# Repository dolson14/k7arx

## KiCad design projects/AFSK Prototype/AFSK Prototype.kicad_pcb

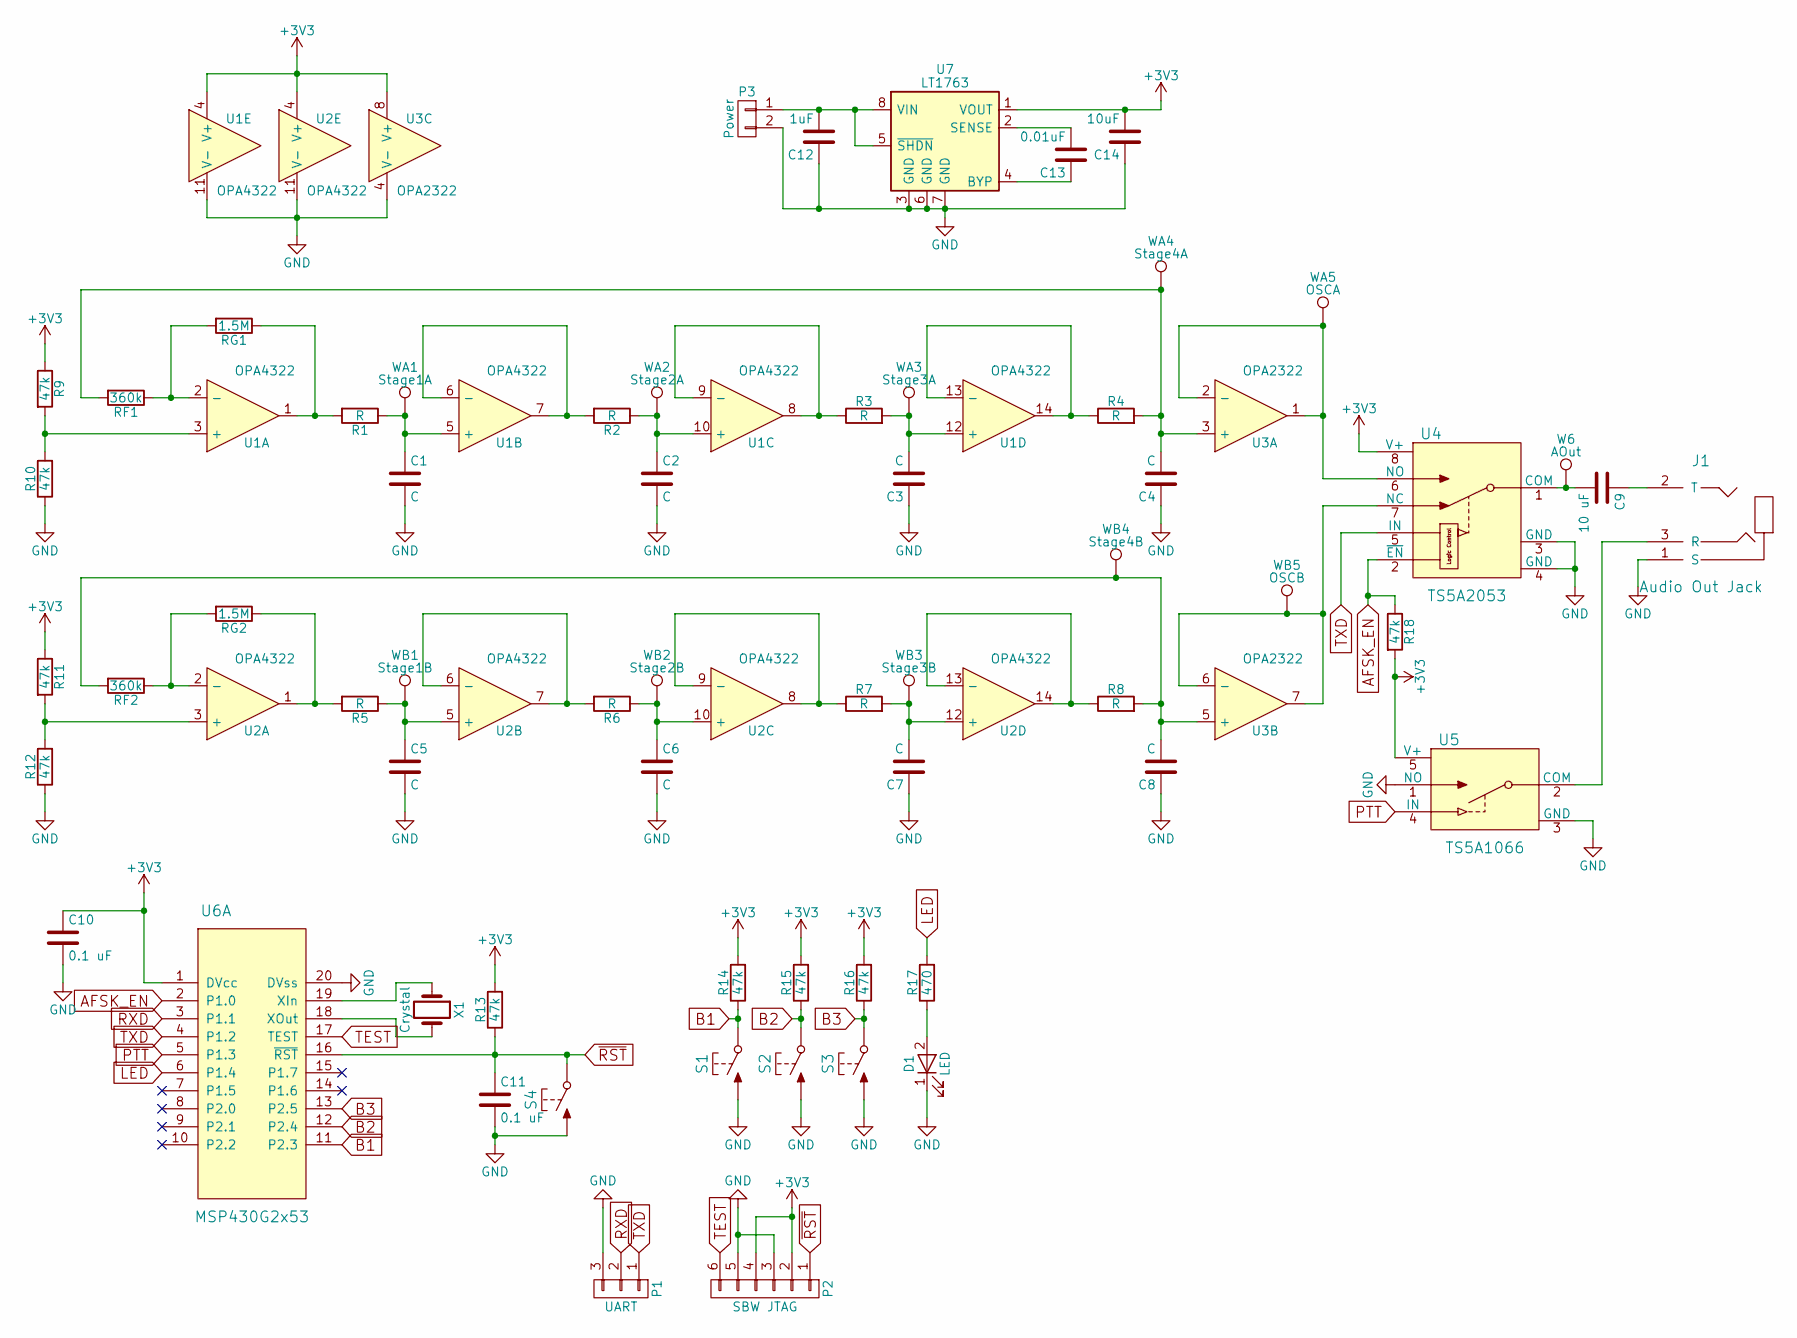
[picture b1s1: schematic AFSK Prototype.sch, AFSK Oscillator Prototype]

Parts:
C1, C2, C3, C4, C5, C6, C7, C8: C; C_0805_HandSoldering
C9: 10 uF; C_0805_HandSoldering
C10, C11: 0.1 uF; C_0805_HandSoldering
C12: 1uF; C_0805_HandSoldering
C13: 0.01uF; C_0805_HandSoldering
C14: 10uF; C_0805_HandSoldering
D1: LED; LED-0805
J1: Audio Out Jack; Jack-TRS-SJ1-3523N
P1: UART; Pin_Header_Straight_1x03
P2: SBW JTAG; Tag-Connect_TC2030-NL
P3: Power; Pin_Header_Straight_1x02
R1, R2, R3, R4, R5, R6, R7, R8: R; R_0805_HandSoldering
R9, R10, R11, R12, R13, R14, R15, R16, R18: 47k; R_0805_HandSoldering
R17: 470; R_0805_HandSoldering
RF1, RF2: 360k; R_0805_HandSoldering
RG1, RG2: 1.5M; R_0805_HandSoldering
S1, S2, S3, S4: TactileSwitch_NO; SPST-EVQ2
U1, U2: OPA4322; PW-14
U3: OPA2322; D
U4: TS5A2053; DCT
U5: TS5A1066; DBV
U6: MSP430G2x53; PW-20
U7: LT1763; SOIC-8-N
W6: AOut; Test_Point
WA1: Stage1A; Test_Point
WA2: Stage2A; Test_Point
WA3: Stage3A; Test_Point
WA4: Stage4A; Test_Point
WA5: OSCA; Test_Point
WB1: Stage1B; Test_Point
WB2: Stage2B; Test_Point
WB3: Stage3B; Test_Point
WB4: Stage4B; Test_Point
WB5: OSCB; Test_Point
X1: Crystal; XTAL-CMR200T

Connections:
+3V3: C10.1, C14.2, P2.2, P2.4, R9.1, R11.1, R13.2, R14.2, R15.2, R16.2, R18.2, U1.4 (V+), U2.4 (V+), U3.8 (V+), U4.8 (V+), U5.5 (V+), U6.1 (DVcc), U7.1 (VOUT)
AFSK_EN: R18.1, U4.2 (~EN), U6.2 (P1.0)
B1: R14.1, S1.2 (COM), U6.11 (P2.3)
B2: R15.1, S2.2 (COM), U6.12 (P2.4)
B3: R16.1, S3.2 (COM), U6.13 (P2.5)
GND: C1.2, C2.2, C3.1, C4.1, C5.2, C6.2, C7.1, C8.1, C10.2, C11.2, C12.1, C14.1, D1.1 (K), J1.1 (S), P1.3, P2.3, P2.5, P3.2, R10.1, R12.1, S1.1 (NO), S2.1 (NO), S3.1 (NO), S4.1 (NO), U1.11 (V-), U2.11 (V-), U3.4 (V-), U4.3 (GND), U4.4 (GND), U5.1 (NO), U5.3 (GND), U6.20 (DVss), U7.3 (GND), U7.6 (GND), U7.7 (GND)
LED: R17.2, U6.6 (P1.4)
unnamed: C1.1, R1.1, U1.5 (+), WA1.1
unnamed: C2.1, R2.1, U1.10 (+), WA2.1
unnamed: C3.2, R3.2, U1.12 (+), WA3.1
unnamed: C4.2, R4.2, RF1.2, U3.3 (+), WA4.1
unnamed: C5.1, R5.1, U2.5 (+), WB1.1
unnamed: C6.1, R6.1, U2.10 (+), WB2.1
unnamed: C7.2, R7.2, U2.12 (+), WB3.1
unnamed: C8.2, R8.2, RF2.2, U3.5 (+), WB4.1
unnamed: C9.1, J1.2 (T)
unnamed: C9.2, U4.1 (COM), W6.1
unnamed: C12.2, P3.1, U7.5 (~SHDN), U7.8 (VIN)
unnamed: C13.1, U7.4 (BYP)
unnamed: C13.2, U7.2 (SENSE)
unnamed: D1.2 (A), R17.1
unnamed: J1.3 (R), U5.2 (COM)
unnamed: R1.2, RG1.1, U1.1
unnamed: R2.2, U1.6 (-), U1.7
unnamed: R3.1, U1.8, U1.9 (-)
unnamed: R4.1, U1.13 (-), U1.14
unnamed: R5.2, RG2.1, U2.1
unnamed: R6.2, U2.6 (-), U2.7
unnamed: R7.1, U2.8, U2.9 (-)
unnamed: R8.1, U2.13 (-), U2.14
unnamed: R9.2, R10.2, U1.3 (+)
unnamed: R11.2, R12.2, U2.3 (+)
unnamed: RF1.1, RG1.2, U1.2 (-)
unnamed: RF2.1, RG2.2, U2.2 (-)
unnamed: U3.1, U3.2 (-), U4.6 (NO), WA5.1
unnamed: U3.6 (-), U3.7, U4.7 (NC), WB5.1
unnamed: U6.18 (XOut), X1.2
unnamed: U6.19 (XIn), X1.1
PTT: U5.4 (IN), U6.5 (P1.3)
RXD: P1.2, U6.3 (P1.1)
TEST: P2.6, U6.17 (TEST)
TXD: P1.1, U4.5 (IN), U6.4 (P1.2)
~RST: C11.1, P2.1, R13.1, S4.2 (COM), U6.16 (~RST)

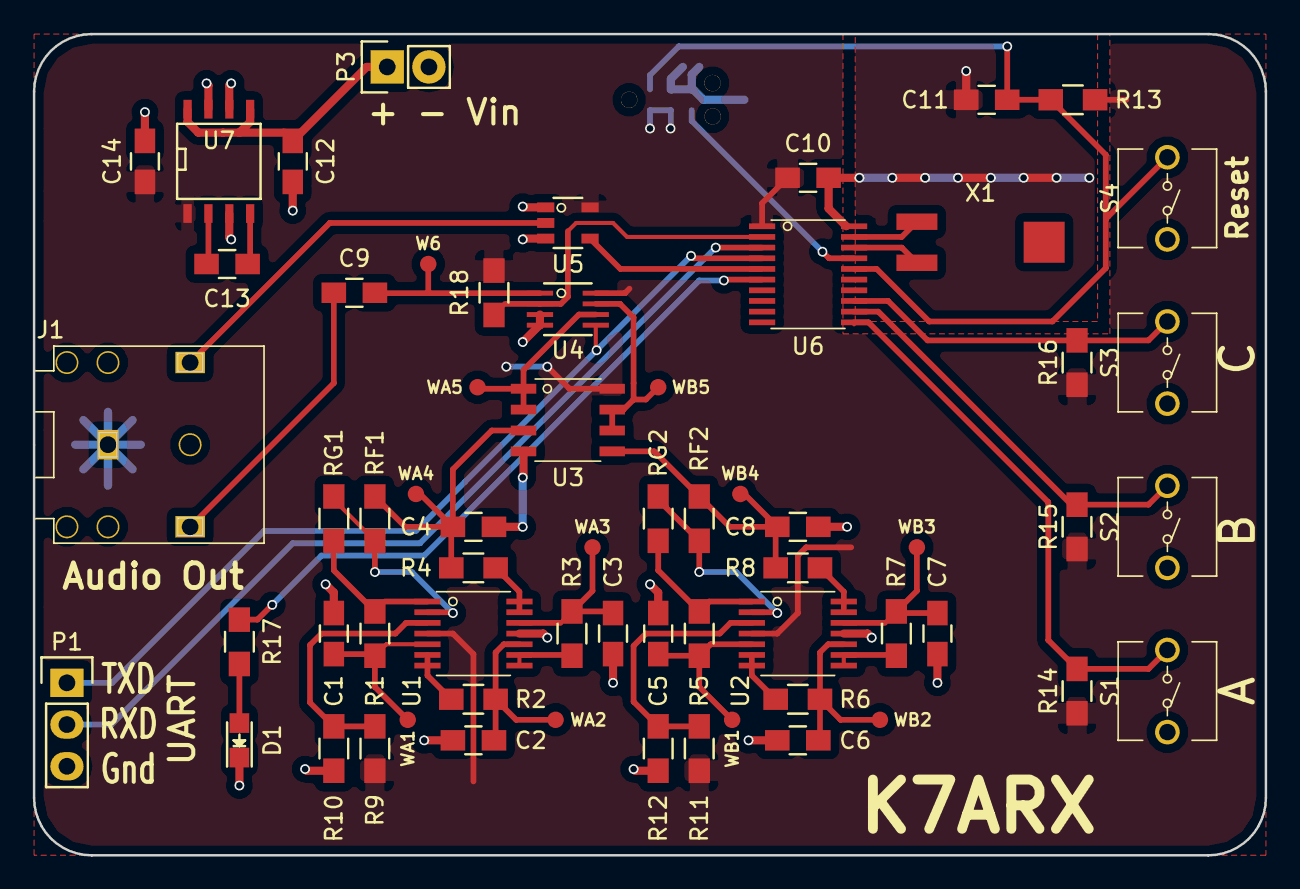
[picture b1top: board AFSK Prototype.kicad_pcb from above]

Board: 2 copper layers, 75.0 x 50.0 mm, 64 parts (1 on the bottom side), 43 nets.

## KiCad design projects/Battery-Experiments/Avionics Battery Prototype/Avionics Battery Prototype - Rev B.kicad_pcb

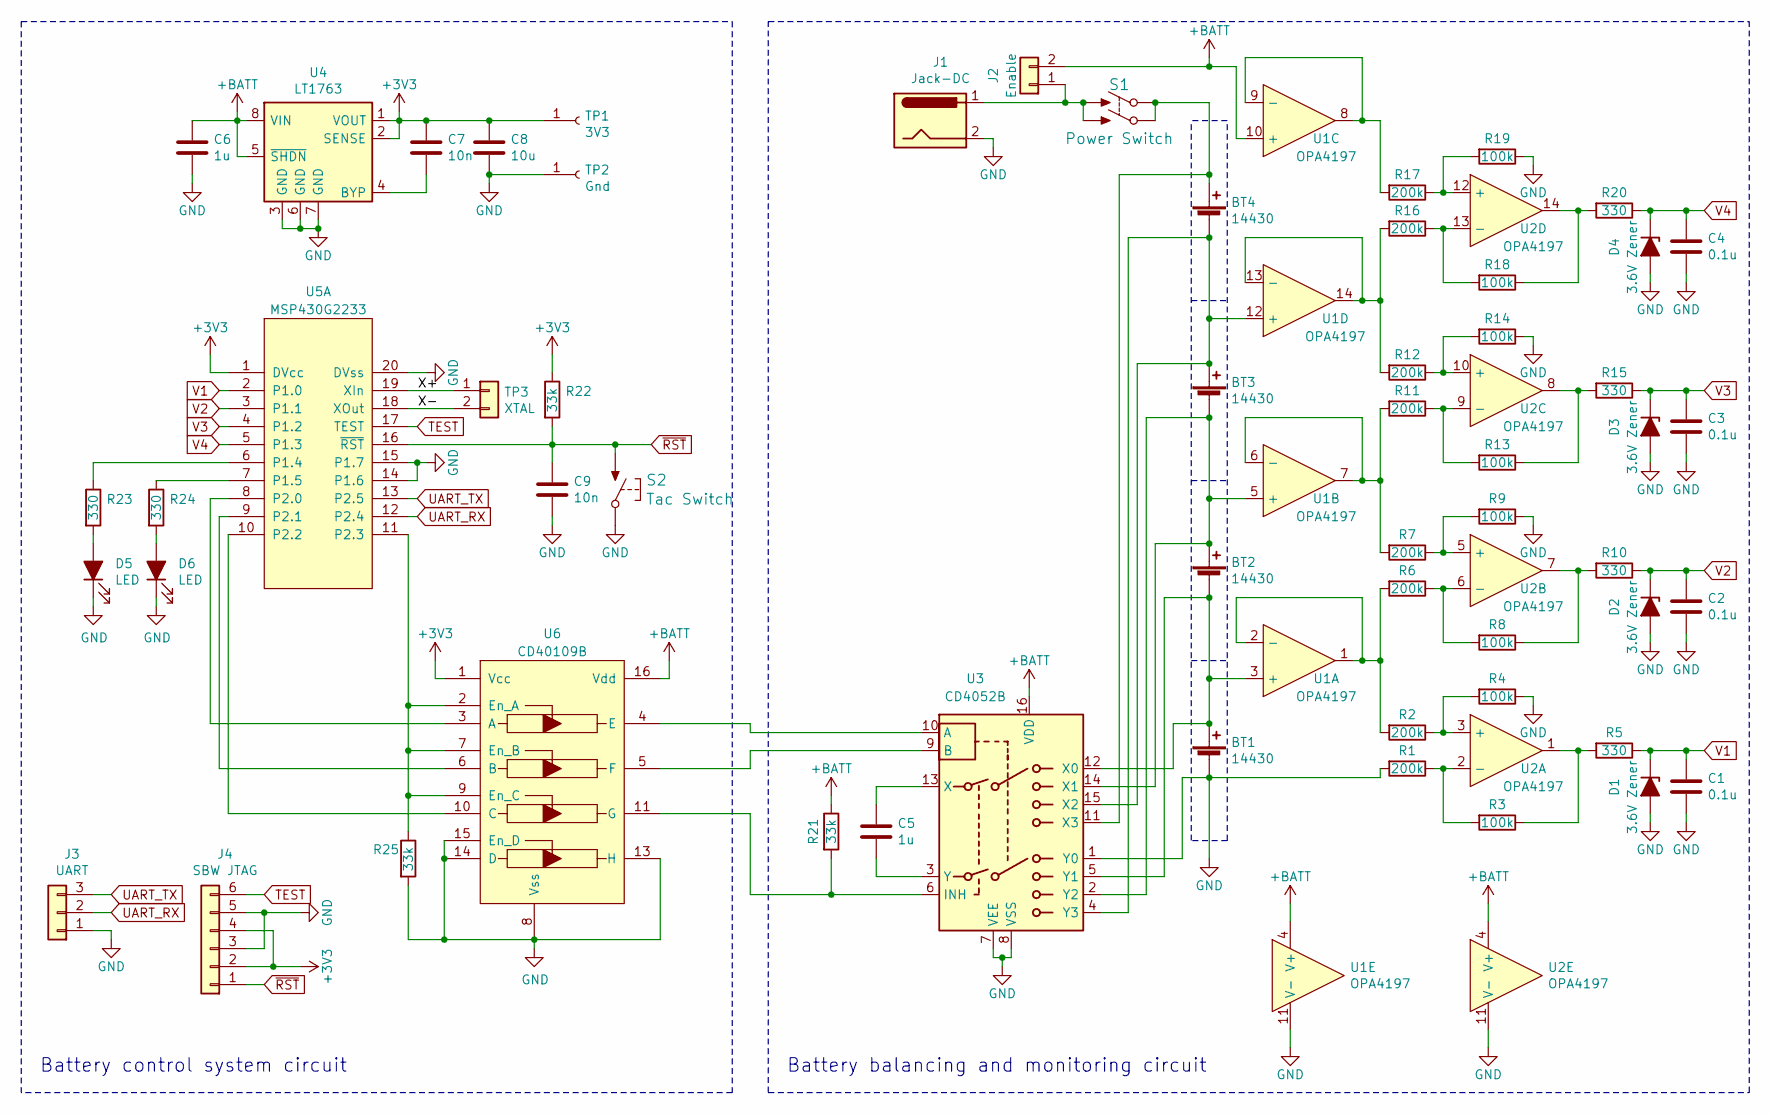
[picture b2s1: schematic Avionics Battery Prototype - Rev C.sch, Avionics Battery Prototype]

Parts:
BT1, BT2, BT3, BT4: 14430; Keystone-92 Battery_Contact 14430
C1, C2, C3, C4: 0.1u; C_1206_HandSoldering
C5, C6: 1u; C_1206_HandSoldering
C7, C9: 10n; C_1206_HandSoldering
C8: 10u; C_1206_HandSoldering
D1, D2, D3, D4: 3.6V Zener; D_SOD-123F
D5, D6: LED; LED_1206_HandSoldering
J1: Jack-DC; Anderson_PowerPole_PCB_2H1V
J2: Enable; Pin_Header_Straight_1x02_Pitch2.54mm
J3: UART; Pin_Header_Straight_1x03_Pitch2.54mm
J4: SBW JTAG; Tag-Connect_TC2030-NL
R1, R2, R6, R7, R11, R12, R16, R17: 200k; R_1206_HandSoldering
R3, R4, R8, R9, R13, R14, R18, R19: 100k; R_1206_HandSoldering
R5, R10, R15, R20, R23, R24: 330; R_1206_HandSoldering
R21, R22, R25: 33k; R_1206_HandSoldering
S1: Power Switch; PB400 DPST Pushbutton Switch
S2: Tac Switch; EVQ2_Momentary_Switch
TP1: 3V3; Pin_Header_Straight_1x01_Pitch2.54mm
TP2: Gnd; Pin_Header_Straight_1x01_Pitch2.54mm
TP3: XTAL; 8MM-11 2-pin PCB socket
U1, U2: OPA4197; SOIC-14_N
U3: CD4052B; SO-16-N
U4: LT1763; SOIC-8-N
U5: MSP430G2233; SSOP-20
U6: CD40109B; SO-16-N

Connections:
+3V3: C7.1, C8.1, J4.2, J4.4, R22.1, TP1.1, U4.1 (VOUT), U4.2 (SENSE), U5.1 (DVcc), U6.1 (Vcc)
+BATT: C6.1, J2.2, R21.1, U1.4 (V+), U1.10 (+), U2.4 (V+), U3.16 (VDD), U4.5 (~SHDN), U4.8 (VIN), U6.16 (Vdd)
unnamed: BT1.1 (+), BT2.2 (-), U1.3 (+), U3.5 (Y1), U3.12 (X0)
unnamed: BT2.1 (+), BT3.2 (-), U1.5 (+), U3.2 (Y2), U3.14 (X1)
unnamed: BT3.1 (+), BT4.2 (-), U1.12 (+), U3.4 (Y3), U3.15 (X2)
unnamed: BT4.1 (+), S1.2 (COM1), S1.4 (COM2), U3.11 (X3)
unnamed: C5.1, U3.13 (X)
unnamed: C5.2, U3.3 (Y)
unnamed: C7.2, U4.4 (BYP)
unnamed: D5.2 (A), R23.2
unnamed: D6.2 (A), R24.2
unnamed: J1.1, J2.1, S1.1 (NO1), S1.3 (NO2)
unnamed: R1.1, R3.2, U2.2 (-)
unnamed: R2.1, R4.2, U2.3 (+)
unnamed: R2.2, R6.2, U1.1, U1.2 (-)
unnamed: R3.1, R5.2, U2.1
unnamed: R6.1, R8.2, U2.6 (-)
unnamed: R7.1, R9.2, U2.5 (+)
unnamed: R8.1, R10.2, U2.7
unnamed: R11.1, R13.2, U2.9 (-)
unnamed: R7.2, R11.2, U1.6 (-), U1.7
unnamed: R12.1, R14.2, U2.10 (+)
unnamed: R12.2, R16.2, U1.13 (-), U1.14
unnamed: R13.1, R15.2, U2.8
unnamed: R16.1, R18.2, U2.13 (-)
unnamed: R17.1, R19.2, U2.12 (+)
unnamed: R17.2, U1.8, U1.9 (-)
unnamed: R18.1, R20.2, U2.14
unnamed: R21.2, U3.6 (INH), U6.11 (G)
unnamed: R23.1, U5.6 (P1.4)
unnamed: R24.1, U5.7 (P1.5)
unnamed: R25.1, U5.11 (P2.3), U6.2 (En_A), U6.7 (En_B), U6.9 (En_C)
unnamed: U3.9 (B), U6.5 (F)
unnamed: U3.10 (A), U6.4 (E)
unnamed: U5.8 (P2.0), U6.3 (A)
unnamed: U5.9 (P2.1), U6.6 (B)
unnamed: U5.10 (P2.2), U6.10 (C)
TEST: J4.6, U5.17 (TEST)
UART_RX: J3.2, U5.12 (P2.4)
UART_TX: J3.3, U5.13 (P2.5)
V1: C1.1, D1.1 (K), R5.1, U5.2 (P1.0)
V2: C2.1, D2.1 (K), R10.1, U5.3 (P1.1)
V3: C3.1, D3.1 (K), R15.1, U5.4 (P1.2)
V4: C4.1, D4.1 (K), R20.1, U5.5 (P1.3)
~RST: C9.1, J4.1, R22.2, S2.1 (NO), U5.16 (~RST)

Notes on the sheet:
Battery balancing and monitoring circuit
Battery control system circuit

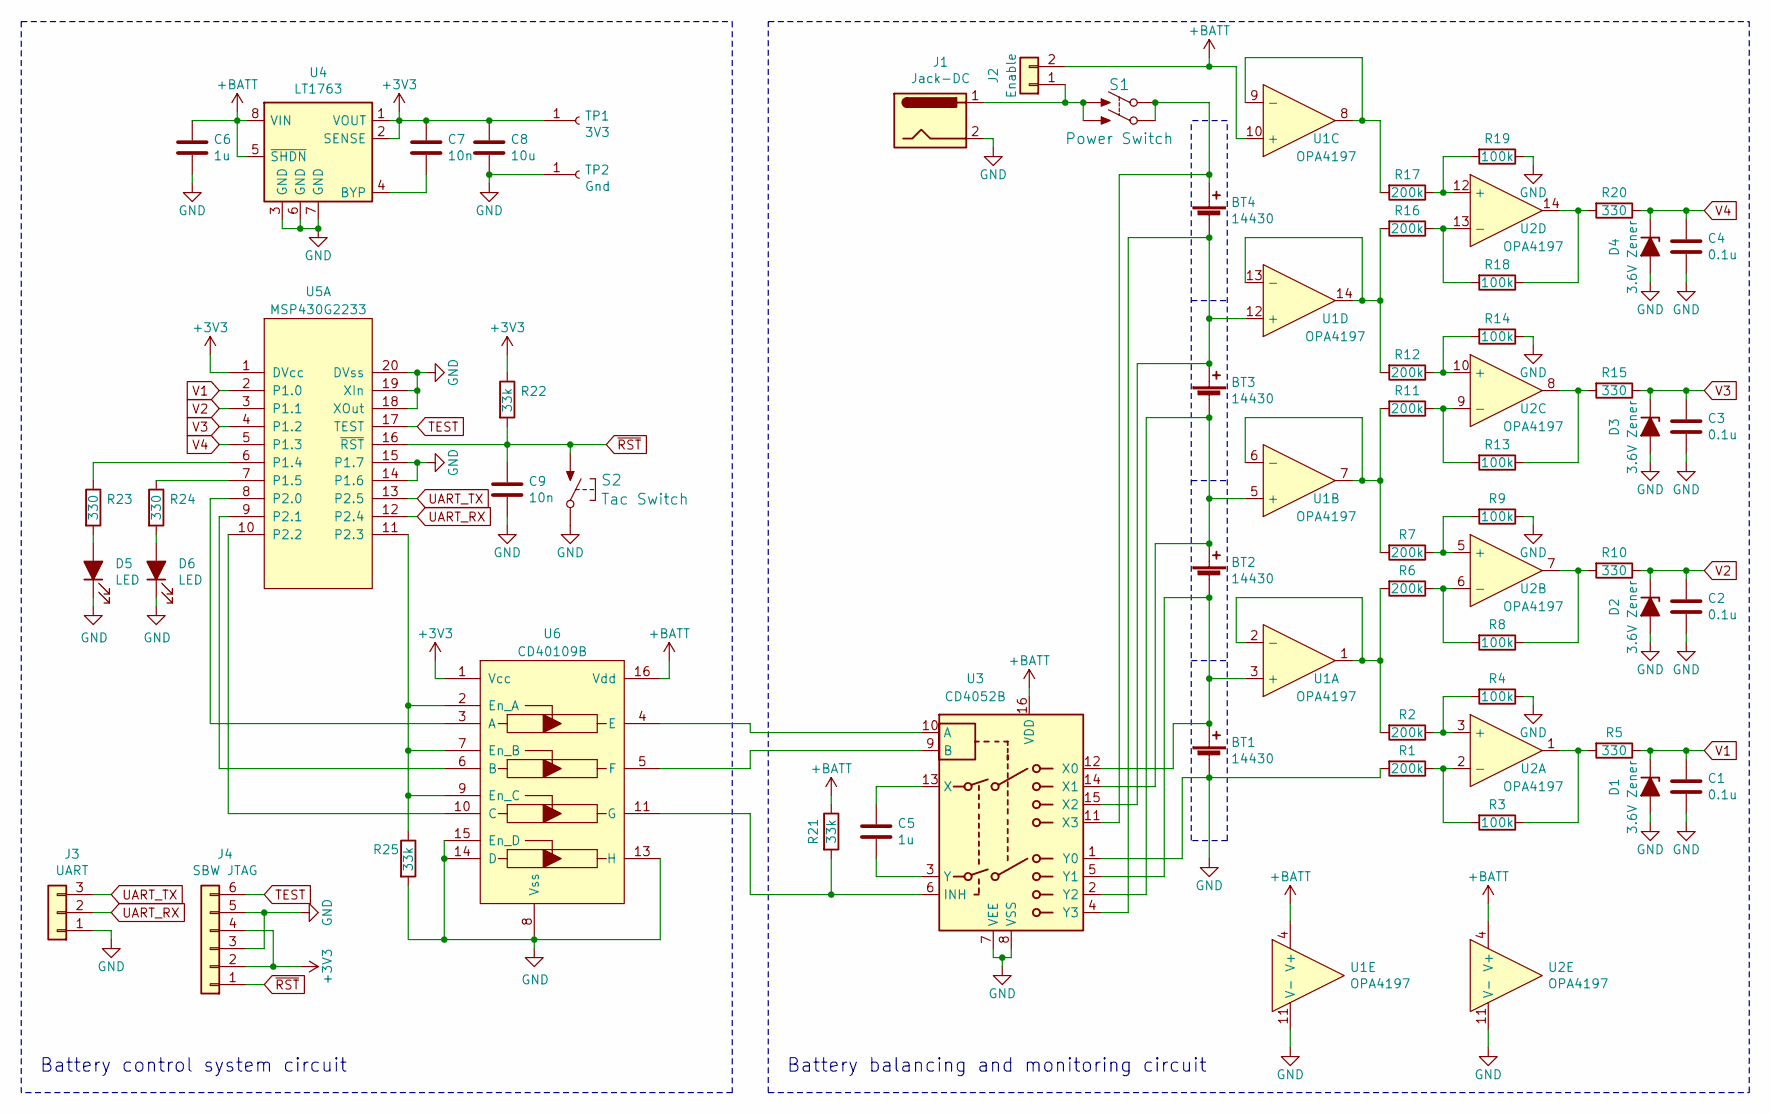
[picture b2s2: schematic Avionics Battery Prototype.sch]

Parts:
BT1, BT2, BT3, BT4: 14430; Keystone-92 Battery_Contact 14430
C1, C2, C3, C4: 0.1u; C_1206_HandSoldering
C5, C6: 1u; C_1206_HandSoldering
C7, C9: 10n; C_1206_HandSoldering
C8: 10u; C_1206_HandSoldering
D1, D2, D3, D4: 3.6V Zener; D_SOD-123F
D5, D6: LED; LED_1206_HandSoldering
J1: Jack-DC; Banana_Jack_2Pin
J2: Enable; Pin_Header_Straight_1x02_Pitch2.54mm
J3: UART; Pin_Header_Straight_1x03_Pitch2.54mm
J4: SBW JTAG; Tag-Connect_TC2030-NL
R1, R2, R6, R7, R11, R12, R16, R17: 200k; R_1206_HandSoldering
R3, R4, R8, R9, R13, R14, R18, R19: 100k; R_1206_HandSoldering
R5, R10, R15, R20, R23, R24: 330; R_1206_HandSoldering
R21, R22, R25: 33k; R_1206_HandSoldering
S1: Power Switch; PB400 DPST Pushbutton Switch
S2: Tac Switch; EVQ2_Momentary_Switch
TP1: 3V3; Pin_Header_Straight_1x01_Pitch2.54mm
TP2: Gnd; Pin_Header_Straight_1x01_Pitch2.54mm
U1, U2: OPA4197; SOIC-14_N
U3: CD4052B; SO-16-N
U4: LT1763; SOIC-8-N
U5: MSP430G2233; SSOP-20
U6: CD40109B; SO-16-N

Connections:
+3V3: C7.1, C8.1, J4.2, J4.4, R22.1, TP1.1, U4.1 (VOUT), U4.2 (SENSE), U5.1 (DVcc), U6.1 (Vcc)
+BATT: C6.1, J2.2, R21.1, U1.4 (V+), U1.10 (+), U2.4 (V+), U3.16 (VDD), U4.5 (~SHDN), U4.8 (VIN), U6.16 (Vdd)
unnamed: BT1.1 (+), BT2.2 (-), U1.3 (+), U3.5 (Y1), U3.12 (X0)
unnamed: BT2.1 (+), BT3.2 (-), U1.5 (+), U3.2 (Y2), U3.14 (X1)
unnamed: BT3.1 (+), BT4.2 (-), U1.12 (+), U3.4 (Y3), U3.15 (X2)
unnamed: BT4.1 (+), S1.2 (COM1), S1.4 (COM2), U3.11 (X3)
unnamed: C5.1, U3.13 (X)
unnamed: C5.2, U3.3 (Y)
unnamed: C7.2, U4.4 (BYP)
unnamed: D5.2 (A), R23.2
unnamed: D6.2 (A), R24.2
unnamed: J1.1, J2.1, S1.1 (NO1), S1.3 (NO2)
unnamed: R1.1, R3.2, U2.2 (-)
unnamed: R2.1, R4.2, U2.3 (+)
unnamed: R2.2, R6.2, U1.1, U1.2 (-)
unnamed: R3.1, R5.2, U2.1
unnamed: R6.1, R8.2, U2.6 (-)
unnamed: R7.1, R9.2, U2.5 (+)
unnamed: R8.1, R10.2, U2.7
unnamed: R11.1, R13.2, U2.9 (-)
unnamed: R7.2, R11.2, U1.6 (-), U1.7
unnamed: R12.1, R14.2, U2.10 (+)
unnamed: R12.2, R16.2, U1.13 (-), U1.14
unnamed: R13.1, R15.2, U2.8
unnamed: R16.1, R18.2, U2.13 (-)
unnamed: R17.1, R19.2, U2.12 (+)
unnamed: R17.2, U1.8, U1.9 (-)
unnamed: R18.1, R20.2, U2.14
unnamed: R21.2, U3.6 (INH), U6.11 (G)
unnamed: R23.1, U5.6 (P1.4)
unnamed: R24.1, U5.7 (P1.5)
unnamed: R25.1, U5.11 (P2.3), U6.2 (En_A), U6.7 (En_B), U6.9 (En_C)
unnamed: U3.9 (B), U6.5 (F)
unnamed: U3.10 (A), U6.4 (E)
unnamed: U5.8 (P2.0), U6.3 (A)
unnamed: U5.9 (P2.1), U6.6 (B)
unnamed: U5.10 (P2.2), U6.10 (C)
TEST: J4.6, U5.17 (TEST)
UART_RX: J3.2, U5.12 (P2.4)
UART_TX: J3.3, U5.13 (P2.5)
V1: C1.1, D1.1 (K), R5.1, U5.2 (P1.0)
V2: C2.1, D2.1 (K), R10.1, U5.3 (P1.1)
V3: C3.1, D3.1 (K), R15.1, U5.4 (P1.2)
V4: C4.1, D4.1 (K), R20.1, U5.5 (P1.3)
~RST: C9.1, J4.1, R22.2, S2.1 (NO), U5.16 (~RST)

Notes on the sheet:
Battery balancing and monitoring circuit
Battery control system circuit

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
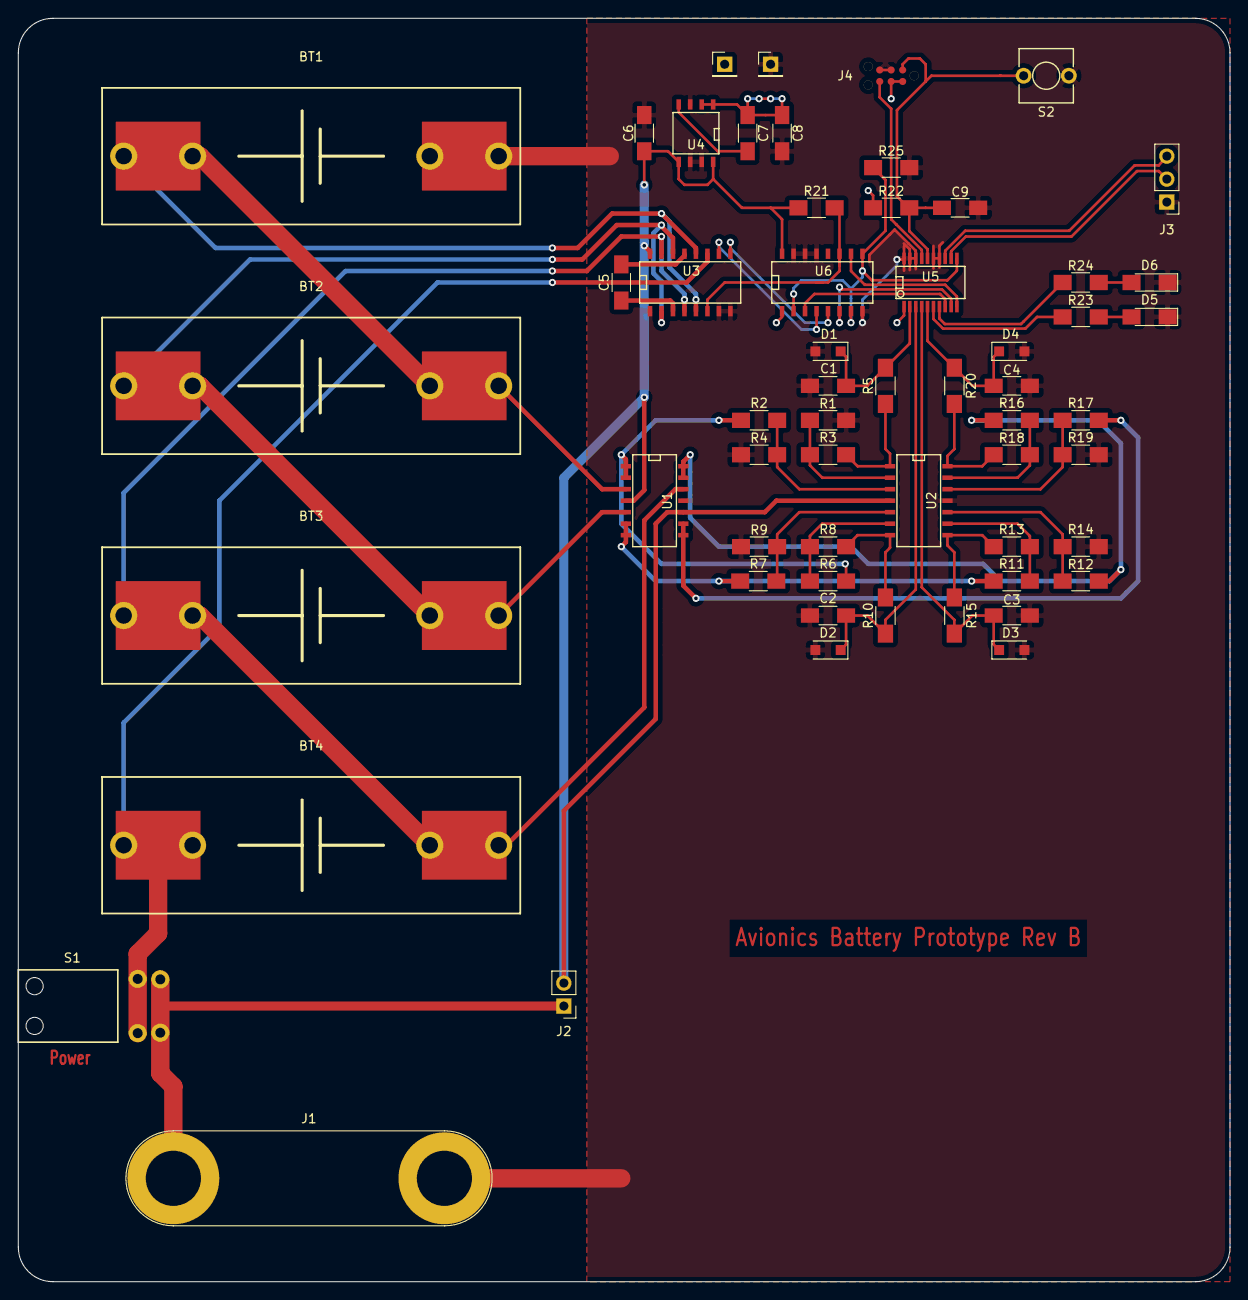
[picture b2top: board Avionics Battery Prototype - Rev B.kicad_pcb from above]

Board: 2 copper layers, 134.0 x 139.7 mm, 58 parts (0 on the bottom side), 46 nets.

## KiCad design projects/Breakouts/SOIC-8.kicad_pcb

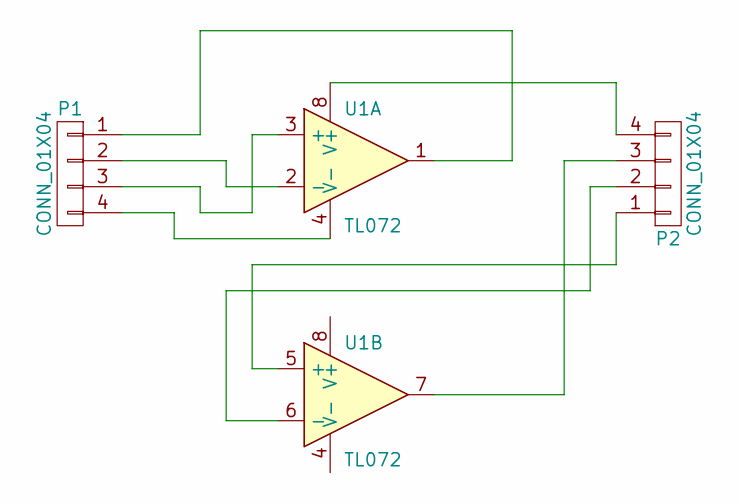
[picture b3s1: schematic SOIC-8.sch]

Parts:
P1, P2: CONN_01X04; Pin_Header_Straight_1x04
U1: TL072; SOIC-8-N2

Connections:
unnamed: P1.1, U1.1
unnamed: P1.2, U1.2 (-)
unnamed: P1.3, U1.3 (+)
unnamed: P1.4, U1.4 (V-)
unnamed: P2.1, U1.5 (+)
unnamed: P2.2, U1.6 (-)
unnamed: P2.3, U1.7
unnamed: P2.4, U1.8 (V+)

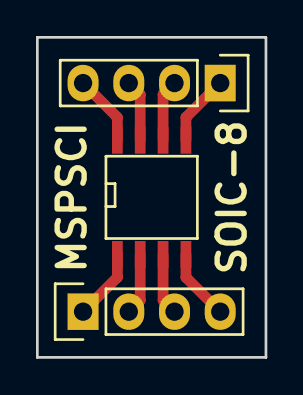
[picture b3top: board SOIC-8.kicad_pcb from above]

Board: 2 copper layers, 12.7 x 17.8 mm, 3 parts (0 on the bottom side), 8 nets.

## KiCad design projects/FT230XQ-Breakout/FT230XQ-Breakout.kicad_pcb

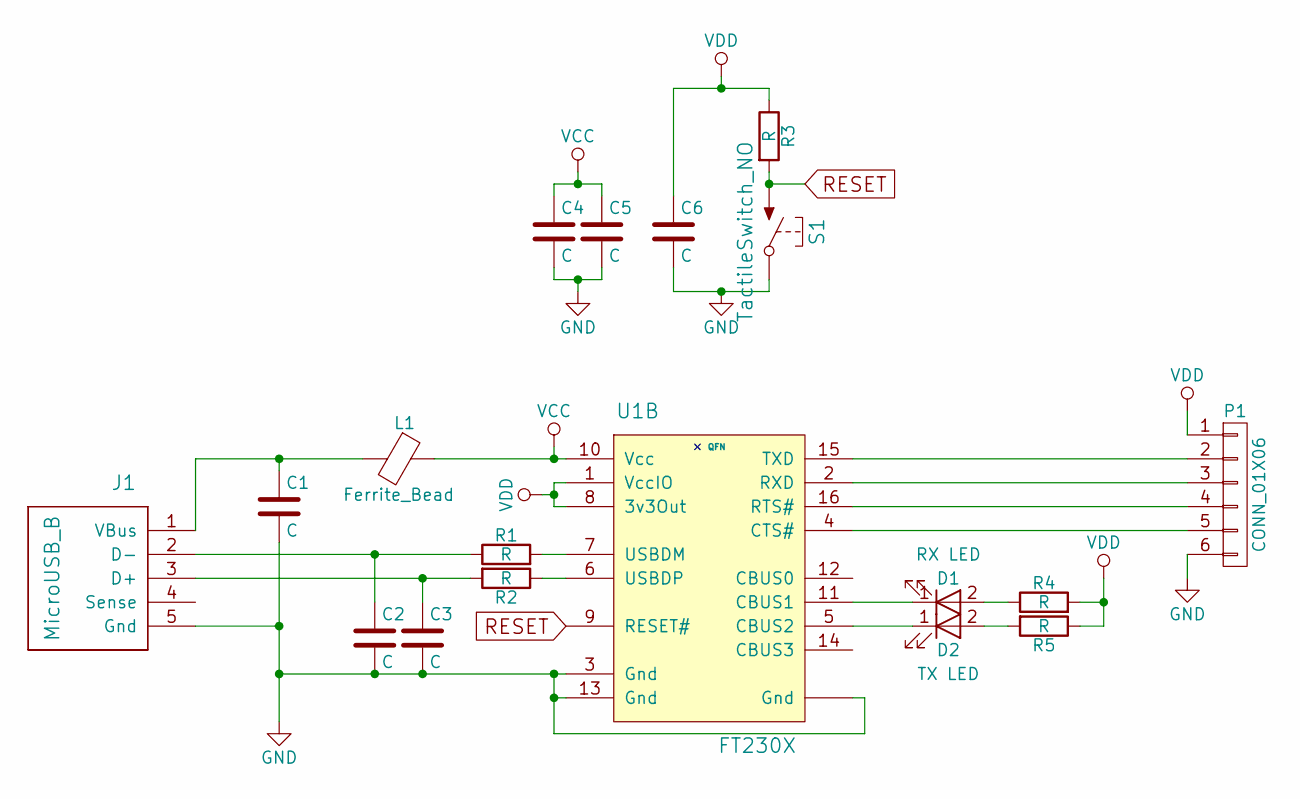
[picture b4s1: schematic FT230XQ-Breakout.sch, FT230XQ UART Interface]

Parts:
C1, C2, C3, C4, C5, C6: C; C_1206_HandSoldering
D1: TX LED; C_0805_HandSoldering
D2: RX LED; C_0805_HandSoldering
J1: MicroUSB_B; MicroUSB-B-RA-FCI
L1: Ferrite_Bead; C_1206_HandSoldering
P1: CONN_01X06; Pin_Header_Straight_1x06
R1, R2, R3, R4, R5: R; R_1206_HandSoldering
S1: TactileSwitch_NO; SPST-EVQ2
U1: FT230X; QFN-16-HS

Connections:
GND: C1.2, C2.2, C3.2, C4.2, C5.2, C6.2, J1.5 (Gnd), J1.~, P1.6, S1.2 (COM), U1.3 (VccIO), U1.13 (Gnd), U1.~ (SSOP)
unnamed: C1.1, J1.1 (VBus), L1.2
unnamed: C2.1, J1.2 (D-), R1.1
unnamed: C3.1, J1.3 (D+), R2.2
unnamed: D1.1 (K), U1.5 (Gnd)
unnamed: D1.2 (A), R5.2
unnamed: D2.1 (K), U1.11 (RESET#)
unnamed: D2.2 (A), R4.1
unnamed: P1.2, U1.15 (CBUS0)
unnamed: P1.3, U1.2 (RTS#)
unnamed: P1.4, U1.16 (CBUS3)
unnamed: P1.5, U1.4 (RXD)
unnamed: R1.2, U1.7 (CBUS2)
unnamed: R2.1, U1.6 (CTS#)
RESET: R3.2, S1.1 (NO), U1.9 (USBDM)
VCC: C4.1, C5.1, L1.1, U1.10 (3v3Out)
VDD: C6.1, P1.1, R3.1, R4.2, R5.1, U1.1 (TXD), U1.8 (USBDP)

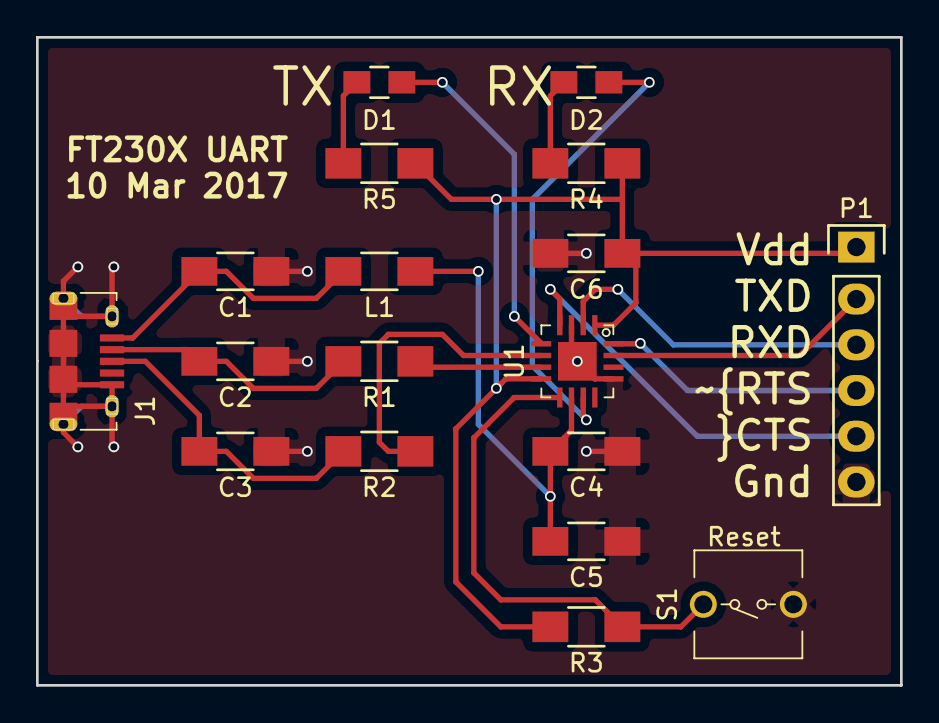
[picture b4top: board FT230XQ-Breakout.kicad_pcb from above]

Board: 2 copper layers, 48.0 x 36.0 mm, 18 parts (0 on the bottom side), 17 nets.

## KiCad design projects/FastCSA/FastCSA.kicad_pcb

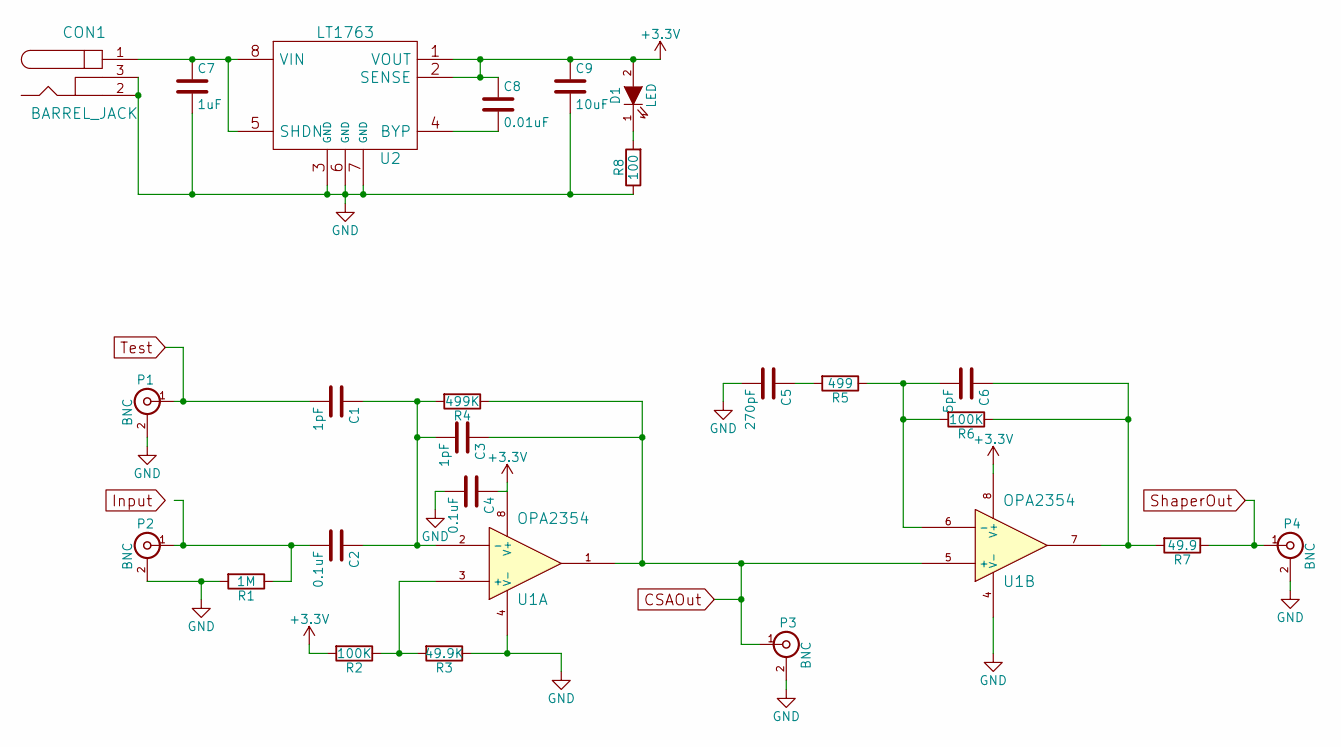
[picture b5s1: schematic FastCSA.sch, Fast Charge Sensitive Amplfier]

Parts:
C1, C3: 1pF; C_1206_HandSoldering
C2, C4: 0.1uF; C_1206_HandSoldering
C5: 270pF; C_1206_HandSoldering
C6: 5pF; C_1206_HandSoldering
C7: 1uF; C_1206_HandSoldering
C8: 0.01uF; C_1206_HandSoldering
C9: 10uF; C_1206_HandSoldering
CON1: BARREL_JACK
D1: LED; LED-3MM
P1, P2, P3, P4: BNC; SMA_Board_Edge
R1: 1M; R_1206_HandSoldering
R2, R6: 100K; R_1206_HandSoldering
R3: 49.9K; R_1206_HandSoldering
R4: 499K; R_1206_HandSoldering
R5: 499; R_1206_HandSoldering
R7: 49.9; R_1206_HandSoldering
R8: 100; R_1206_HandSoldering
U1: OPA2354; SOIC-8-N
U2: LT1763; SOIC-8-N

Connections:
+3V3: C4.1, C8.1, C9.1, D1.2 (A), R2.2, U1.8 (V+), U2.1 (VOUT), U2.2 (SENSE)
CSAOut: C3.1, P3.1 (In), R4.1, U1.1, U1.5 (+)
GND: C4.2, C5.2, C7.2, C9.2, CON1.2, CON1.3, P1.2 (Ext), P2.2 (Ext), P3.2 (Ext), P4.2 (Ext), R1.2, R3.1, R8.1, U1.4 (V-), U2.3 (GND), U2.6 (GND), U2.7 (GND)
unnamed: C1.1, C2.1, C3.2, R4.2, U1.2 (-)
unnamed: C2.2, P2.1 (In), R1.1
unnamed: C5.1, R5.2
unnamed: C6.1, R6.1, R7.2, U1.7
unnamed: C6.2, R5.1, R6.2, U1.6 (-)
unnamed: C7.1, CON1.1, U2.5 (SHDN), U2.8 (VIN)
unnamed: C8.2, U2.4 (BYP)
unnamed: D1.1 (K), R8.2
unnamed: R2.1, R3.2, U1.3 (+)
ShaperOut: P4.1 (In), R7.1
Test: C1.2, P1.1 (In)

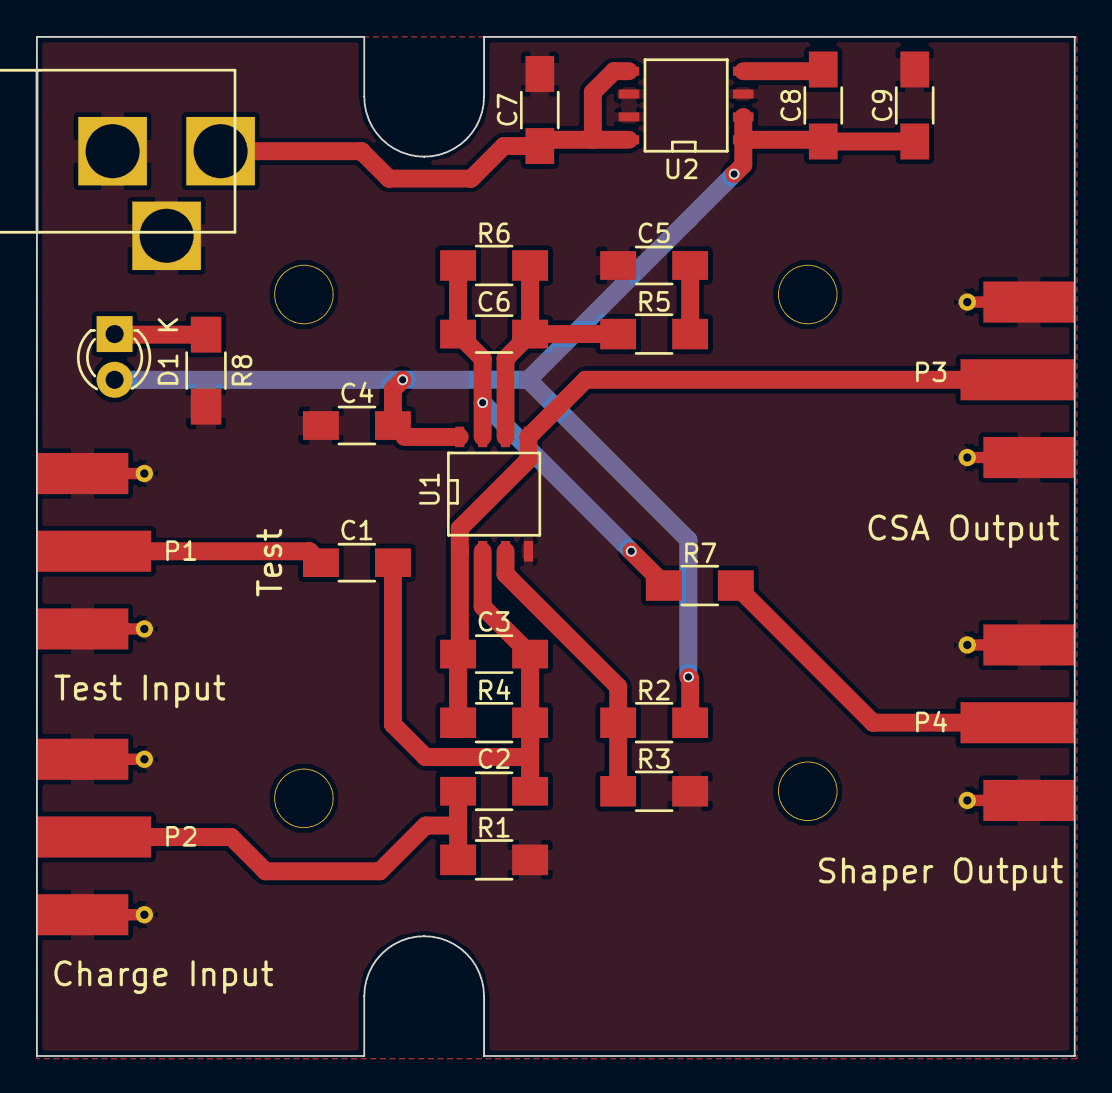
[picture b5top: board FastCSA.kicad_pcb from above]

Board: 2 copper layers, 57.7 x 56.6 mm, 25 parts (0 on the bottom side), 14 nets.
